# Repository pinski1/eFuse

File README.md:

#eFuse

An electronic fuse for high power robotics.

Issue A hardware was commit id: 0dbf9790596710304bc9dd8e25b2f3861c4695b0

##Licence
<br /><span xmlns:dct="http://purl.org/dc/terms/" property="dct:title">eFuse</span> by <a xmlns:cc="http://creativecommons.org/ns#" href="http://wiresandbits.co.uk/" property="cc:attributionName" rel="cc:attributionURL">Pinski1</a> is licensed under a <a rel="license" href="http://creativecommons.org/licenses/by-sa/4.0/">Creative Commons Attribution-ShareAlike 4.0 International License</a>.<br />Based on a work at <a xmlns:dct="http://purl.org/dc/terms/" href="https://github.com/pinski1/eFuse" rel="dct:source">https://github.com/pinski1/eFuse</a>.

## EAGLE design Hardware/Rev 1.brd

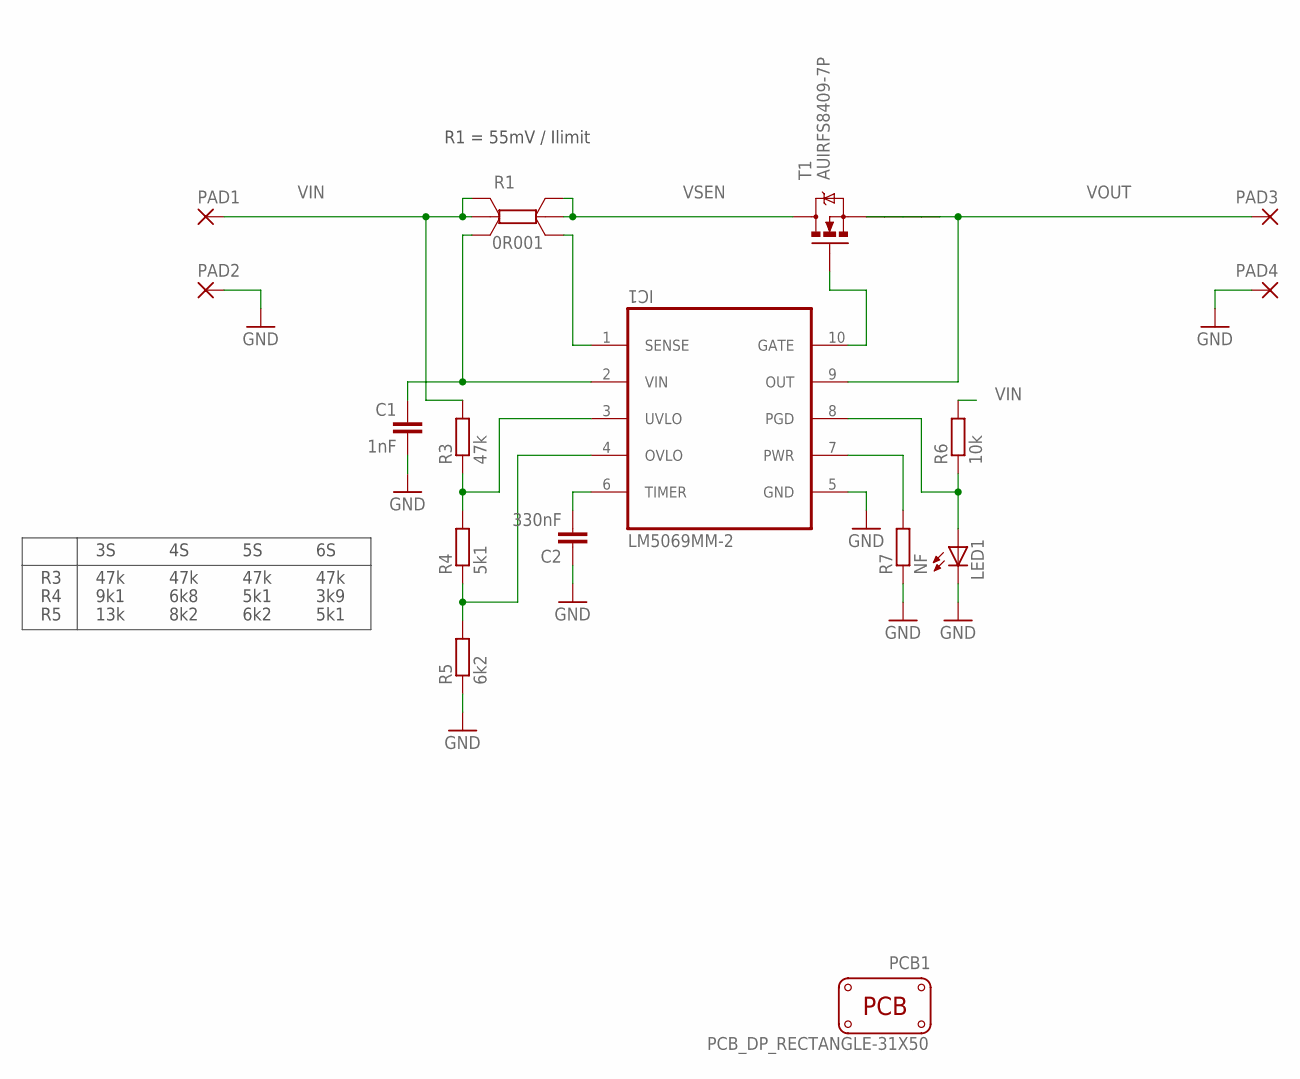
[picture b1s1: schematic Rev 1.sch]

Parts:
C1: 1nF; C0603; MPN VJ0603Y102KXBAC31
C2: 330nF; C0603; MPN C1608X7R1E334K080AC
IC1: LM5069MM-2; SOP50P490X110-10N
LED1: LED-0805; LED-805; MPN SML-211UTT86K
PAD1, PAD2, PAD3, PAD4: SMD7; SMD3,81-7,62
PCB1: PCB_DP_RECTANGLE-31X50; DP5031_V1
R1: 0R001; OARS_SP_4PAD; MPN OARSXPR001FLF
R3: 47k; R0603; MPN RC0603FR-0747KL
R4: 5k1; R0603; MPN CRCW02015K10FNED
R5: 6k2; R0603; MPN CRCW06036K20FKEA
R6: 10k; R0603; MPN CRGH0603J10K
R7: NF; R0603
T1: AUIRFS8409-7P; TO263-6; MPN AUIRFS8409-7P

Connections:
CTIMER: C2.2, IC1.6 (TIMER)
GATE_DRIVE: IC1.10 (GATE), T1.1 (G)
GND: C1.2, C2.1, IC1.5 (GND), LED1.C, PAD2.1, PAD4.1, R5.1, R7.1
OVLO: IC1.4 (OVLO), R4.1, R5.2
PGD: IC1.8 (PGD), LED1.A, R6.1
POWER: IC1.7 (PWR), R7.2
SENSE: IC1.1 (SENSE), R1.AK
UVLO: IC1.3 (UVLO), R3.1, R4.2
VIN: PAD1.1, R1.B1, R1.B2, R3.2, R6.2
VIN_K: C1.1, IC1.2 (VIN), R1.BK
VOUT: IC1.9 (OUT), PAD3.1, T1.2 (S), T1.3 (S), T1.4 (S), T1.5 (S), T1.6 (S)
VSEN: R1.A1, R1.A2, T1.TH (D)

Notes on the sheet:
47k
6k8
8k2
9k1
13k
6k2
5k1
3k9
R1 = 55mV / Ilimit

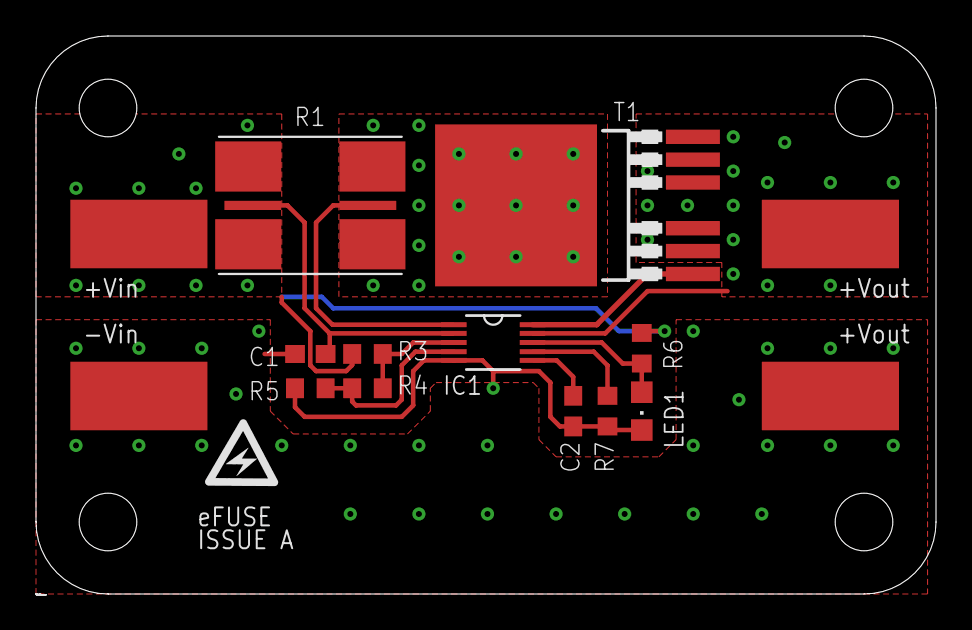
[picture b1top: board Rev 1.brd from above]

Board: 2 copper layers, 50.0 x 31.0 mm, 16 parts (0 on the bottom side), 12 nets.

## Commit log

2015-10-12 Add image and current limit maths.
